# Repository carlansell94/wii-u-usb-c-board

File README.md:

A small board designed to replace the proprietary Wii U dock charging port with a USB type C port.

Features:
* Includes pads for 5.1k&#937; resistors, to allow the use of 'smart' chargers.
* Pads on the + output allow the addition of a switch - bridge these pads with a 0&#937; resistor if you're not using one.
* Board is a near drop-in replacement for the original - only a small amount of sanding inside the dock is required.
* No alteration to the outside of the dock is necessary (unless you add a switch).

A switchless version is also available, which removes the need to bridge the switch pads should you choose not to use one.

Included in this repository are the KiCAD files for this design. If you're only interested in having the board manufactured, gerbers are available under 'releases'.

Parts List:
* 1x 16 pin USB type C port
* 1x 0603 0&#937; resistor/1x 2 pin switch
* 2x 0603 5.1k&#937; resistors (optional)

A tri-wing screwdriver is required, to remove the dock base.

When having the board manufactured, ensure they offer a 0.8mm board thickness - I used OSH Park for mine.

For more information, take a look at [my blog post](https://qubitsandbytes.co.uk/post/convert-a-wii-u-dock-to-usb-c).

## Images
KiCAD render:

Dock with added switch:

## KiCAD
The files in this project were created using KiCAD 6, which introduced a new file format not compatible with older versions. Ensure you are using KiCAD 6 if you wish to open the files.

In addition, the USB Type C port pictured in the 3D render can be found [over here](https://github.com/ai03-2725/Type-C.pretty) - the file you're looking for is 'HRO TYPE-C-31-M-12.step'. It's not required, unless you want to see the part populated using the 3D viewer.

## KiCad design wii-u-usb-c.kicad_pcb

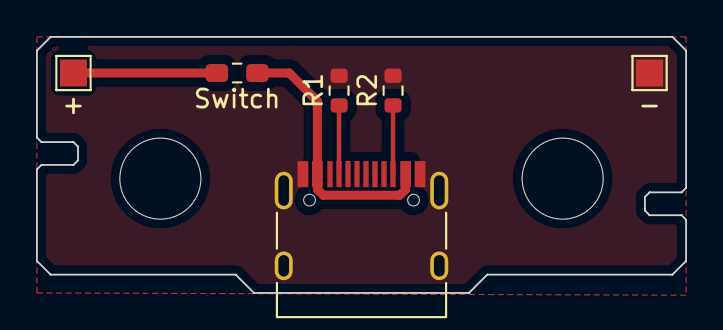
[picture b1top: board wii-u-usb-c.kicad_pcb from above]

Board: 2 copper layers, 36.1 x 14.2 mm, 6 parts (0 on the bottom side), 5 nets.

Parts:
+: +; TestPoint_Pad_1.5x1.5mm
-: -; TestPoint_Pad_1.5x1.5mm
J1: USB_C_Receptacle; USB_C_Receptacle_HRO_TYPE-C-31-M-12
R1, R2: 5.1k; R_0603_1608Metric
Switch: 0; R_0603_1608Metric

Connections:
GND: -.1, J1.A1 (GND), J1.A12 (GND), J1.B1 (GND), J1.B12 (GND), J1.S1 (SHIELD), R1.2, R2.2
unnamed: J1.A4 (VBUS), J1.A9 (VBUS), J1.B4 (VBUS), J1.B9 (VBUS), Switch.1
unnamed: J1.A5 (CC1), R1.1
unnamed: J1.B5 (CC2), R2.1
unnamed: +.1, Switch.2

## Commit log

2022-03-14 Add missing image
2023-10-04 feat: Add switchless version
2023-10-04 feat: Update to KiCAD v7 file format
2023-10-04 docs: Update README
